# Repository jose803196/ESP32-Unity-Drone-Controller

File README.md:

<div align="center">
  <h1>Project: DroneLink Simulator</h1>
  <p>
    <strong>A real-time 3D drone simulator controlled by a custom-built physical interface based on the ESP32 microcontroller.</strong>
  </p>
  <br>
  <p>
    <a href="#-about-the-project">About</a> ·
    <a href="#-features">Features</a> ·
    <a href="#-tech-stack">Tech Stack</a> ·
    <a href="#-getting-started">Getting Started</a> ·
    <a href="#-repository-structure">Structure</a> ·
    <a href="#-author">Author</a>
  </p>
</div>

---

## 📋 About The Project

**DroneLink Simulator** is a comprehensive hardware-in-the-loop project that bridges the gap between physical electronics and virtual simulation. The core idea is to provide an immersive and realistic control experience by flying a 3D drone in a Unity environment using a dedicated hardware controller.

This repository contains everything from the ground up:
*   **Hardware Design:** Custom schematics and PCB layouts for the controller.
*   **Embedded Firmware:** Robust C code for the ESP32 to read sensors and communicate data.
*   **3D Simulation:** A fully functional Unity project that receives and interprets the hardware data to manipulate the drone.
*   **Complete Documentation:** In-depth reports explaining the design and implementation process.

<br>

## ✨ Features

*   **Real-time Control:** Low-latency communication between the ESP32 and Unity via UART.
*   **Intuitive Physical Interface:** Control using a joystick for movement, buttons for altitude and lateral movement.
*   **Realistic Physics:** The drone in Unity is powered by a `Rigidbody` component for believable movement.
*   **Modular Codebase:** Clean and well-documented code in both C (ESP32) and C# (Unity).
*   **Integrated 3D Workflow:** Includes `.blend` files directly within the Unity project for seamless model editing.
*   **Open Source:** Fully documented and ready to be forked, modified, and improved.

<br>

## 🛠️ Tech Stack

This project is built with a combination of hardware and software technologies:

<table>
  <tr>
    <td align="center"><strong>Hardware</strong></td>
    <td align="center"><strong>Firmware</strong></td>
    <td align="center"><strong>Simulation</strong></td>
    <td align="center"><strong>Documentation</strong></td>
  </tr>
  <tr>
    <td>
      <ul>
        <li>ESP32 DevKitC</li>
        <li>MPU-6050 Gyro/Accel</li>
        <li>Analog Joystick</li>
        <li>Push Buttons</li>
        <li>Buzzer</li>
        <li>LED's RGB</li>
        <li>Motor</li>
        <li>BJT transistor</li>
      </ul>
    </td>
    <td>
      <ul>
        <li>C Language</li>
        <li>ESP-IDF Framework</li>
        <li>FreeRTOS</li>
        <li>UART Communication</li>
      </ul>
    </td>
    <td>
      <ul>
        <li>Unity Engine</li>
        <li>C# Language</li>
        <li>Blender (for 3D models)</li>
      </ul>
    </td>
    <td>
      <ul>
        <li>Markdown</li>
        <li>KiCad (for Schematics/PCB)</li>
      </ul>
    </td>
  </tr>
</table>

<br>

## 🚀 Getting Started

Follow these steps to get the project up and running on your local machine.

### Prerequisites

*   **Hardware:** All components listed in `Hardware`.
*   **Software:**
    *   Unity Hub & Unity Editor (version `202X.X.Xf1` recommended).
    *   ESP-IDF (version `vX.X` recommended).

### Installation & Setup

1.  **Clone the Repository**
    ```sh
    git clone https://github.com/jose803196/ESP32-Unity-Drone-Controller
    ```

2.  **Flash the Firmware**
    *   Navigate to the `Firmware_ESP32` and `FIRMWARE_ESP32BRIDGE` directories.
    *   Connect your assembled controller to your computer.
    *   Run `idf.py flash monitor` to build, upload, and view the serial output.

3.  **Run the Unity Simulation**
    *   Open Unity Hub and select "Add project from disk".
    *   Choose the `Unity_Project` folder from this repository.
    *   Once the project is open, navigate to the main scene in `Assets/_Project_DroneSim/Scenes/`.
    *   In the `DroneController` script component, set the `Port Name` to match the one used by your ESP32.
    *   Press **Play**!

<br>

## 📂 Repository Structure

The repository is organized into four main sections for clarity and modularity:

<br>

## 👤 Author

**Jose G. Lopez B.**

*   
*   
*   

---
<div align="center">
  <small>This project was created as part of Project Laboratory.</small>
</div>

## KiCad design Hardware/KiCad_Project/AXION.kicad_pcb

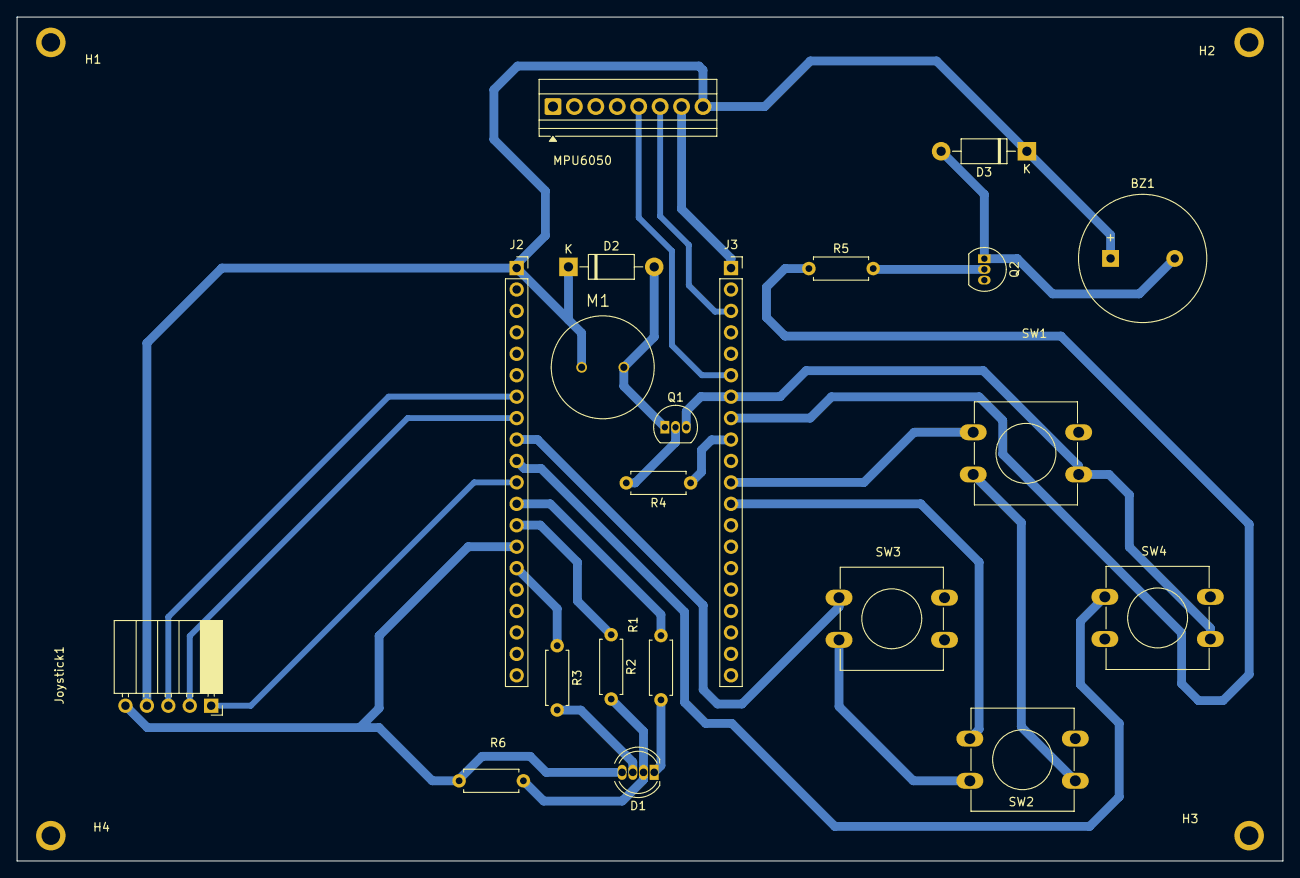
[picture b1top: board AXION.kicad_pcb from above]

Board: 2 copper layers, 150.0 x 100.0 mm, 25 parts (0 on the bottom side), 23 nets.

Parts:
BZ1: Buzzer; Buzzer_15x7.5RM7.6
D1: LED_RGBK; LED_D5.0mm-4_RGB
D2, D3: 1N4007; D_DO-41_SOD81_P10.16mm_Horizontal
H1, H2, H3, H4: MountingHole_2.2mm_M2_ISO7380_Pad
J2, J3: Conn_01x20; PinSocket_1x20_P2.54mm_Vertical
Joystick1: Conn_01x05; PinSocket_1x05_P2.54mm_Horizontal
M1: Motor_DC; XDCR_PS1240P02BT
MPU6050: Conn_01x08; TerminalBlock_Xinya_XY308-2.54-8P_1x08_P2.54mm_Horizontal
Q1, Q2: BC237; TO-92_Inline
R1, R2, R3, R6: 200 Ω; R_Axial_DIN0207_L6.3mm_D2.5mm_P7.62mm_Horizontal
R4, R5: 1 kΩ; R_Axial_DIN0207_L6.3mm_D2.5mm_P7.62mm_Horizontal
SW1: Avanzar; SW_PUSH-12mm
SW2: Retroceder; SW_PUSH-12mm
SW3: Izquierda; SW_PUSH-12mm
SW4: Derecha; SW_PUSH-12mm

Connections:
BUZZER: BZ1.2 (-), D3.2 (A), Q2.1 (C)
GND: D1.4 (K), H1.1, H2.2, H3.3, H4.4, J2.14, J3.1, J3.7, Joystick1.5, MPU6050.7, Q1.3 (E), Q2.3 (E), R6.1, SW1.2, SW2.1, SW3.2, SW4.2
MOTOR: D2.2 (A), M1.2 (-), Q1.1 (C)
unnamed: D1.3 (BA), R3.2
unnamed: D1.2 (GA), R2.2, R6.2
unnamed: D1.1 (RA), R1.2
unnamed: Q1.2 (B), R4.2
unnamed: Q2.2 (B), R5.2
PIN01: BZ1.1 (+), D2.1 (K), D3.1 (K), J2.1, Joystick1.4, M1.1 (+), MPU6050.8
PIN07: J2.7, Joystick1.3
PIN08: J2.8, Joystick1.2
PIN09: J2.9, SW3.1
PIN10: J2.10, SW4.1
PIN11: J2.11, Joystick1.1
PIN12: J2.12, R1.1
PIN13: J2.13, R2.1
PIN15: J2.15, R3.1
PIN27: J3.12, SW2.2
PIN28: J3.11, SW1.1
PIN30: J3.9, R4.1
PIN31: J3.8, R5.1
PIN33: J3.6, MPU6050.5
PIN36: J3.3, MPU6050.6

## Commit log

2025-07-11 Init the project with drone
2025-07-11 fix: Create the Readme file
2025-07-11 fix: update the name in readme
2025-07-11 fix: Create the Hardware folder
2025-07-11 fix: Create the firmware
2025-07-13 fix: update Firmware_ESP32
2025-07-13 fix: Adding bluetooth to Firmware_ESP32
2025-07-14 fix: complete wireless comunication for ESP NOW
2025-07-17 fix: update Unity and ESP32 Controller
2025-07-18 fix: update the code in leds
2025-07-18 fix: update sch and pcb design
2025-07-20 fix: update PCB y schematic design
2025-07-23 fix: update Unity and hardware
2025-07-23 fix: update ESP32 Bridge with alarm
2025-07-23 fix: update PCB
2025-07-28 fix: update MenuNavegator and create PreMenuNavegator
2025-07-31 fix: adding movement to drone
2025-08-01 fix: update the Readme file
2025-08-04 fix: update readme and saves version 1.5
2025-08-04 WIP: Guardado temporal antes de limpiar
2025-08-04 Remove Unity Library files from repository
2025-08-04 Update project settings and packages
2025-08-04 Update gitignore to exclude user-specific settings
2025-08-09 fix: update drone simulate with sensor MPU6050
2025-10-08 fix: update readme and hardware section
2025-10-23 fix: remove comments in code ESP32´s
